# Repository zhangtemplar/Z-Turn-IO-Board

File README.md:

# Z-Turn-IO-Board
my own expansion board which converts the 1.27mm pitch connector to 2.54mm pitch connector for Z-turn board (http://www.myirtech.com/list.asp?id=502) from MYiR

###
A lot of design is borrowed from the IO Cape board (http://www.myirtech.com/list.asp?id=532) of MYiR, where I converts the Connector 1 to 6 PMOD compatible (2.54 mm dual row 12 pin header) headers and 1 40 pin FFC/FPC connector (for LCD); and Connector 2 to 2 PMOD headers plus 2 2.54mm dual row 34 pin header. Especially:

Connector | Comments
--------- | --------
CN1, CN2 | two 1.27mm pitch dual row 80 pin headers from Z-turn board
J1,J2|two 2.54mm pitch dual row 34 pin headers for FPGA differential pin (12 pairs each);
LCD|40 pin FFC/FPC connector;
MISC|PMOD header for I2C;
I2S|PMOD header for I2S and HDMI;
J3, J4, J5, J6|PMOD header for FPGA differential pin (4 pairs each);
ADC|PMOD header for XADC input (two pairs of analog input);
MIO|PMOD header for ARM IO pin (8 pins);
Note|the differential pins is not ready for high speed differential usage yet, as the length is not properly configured.

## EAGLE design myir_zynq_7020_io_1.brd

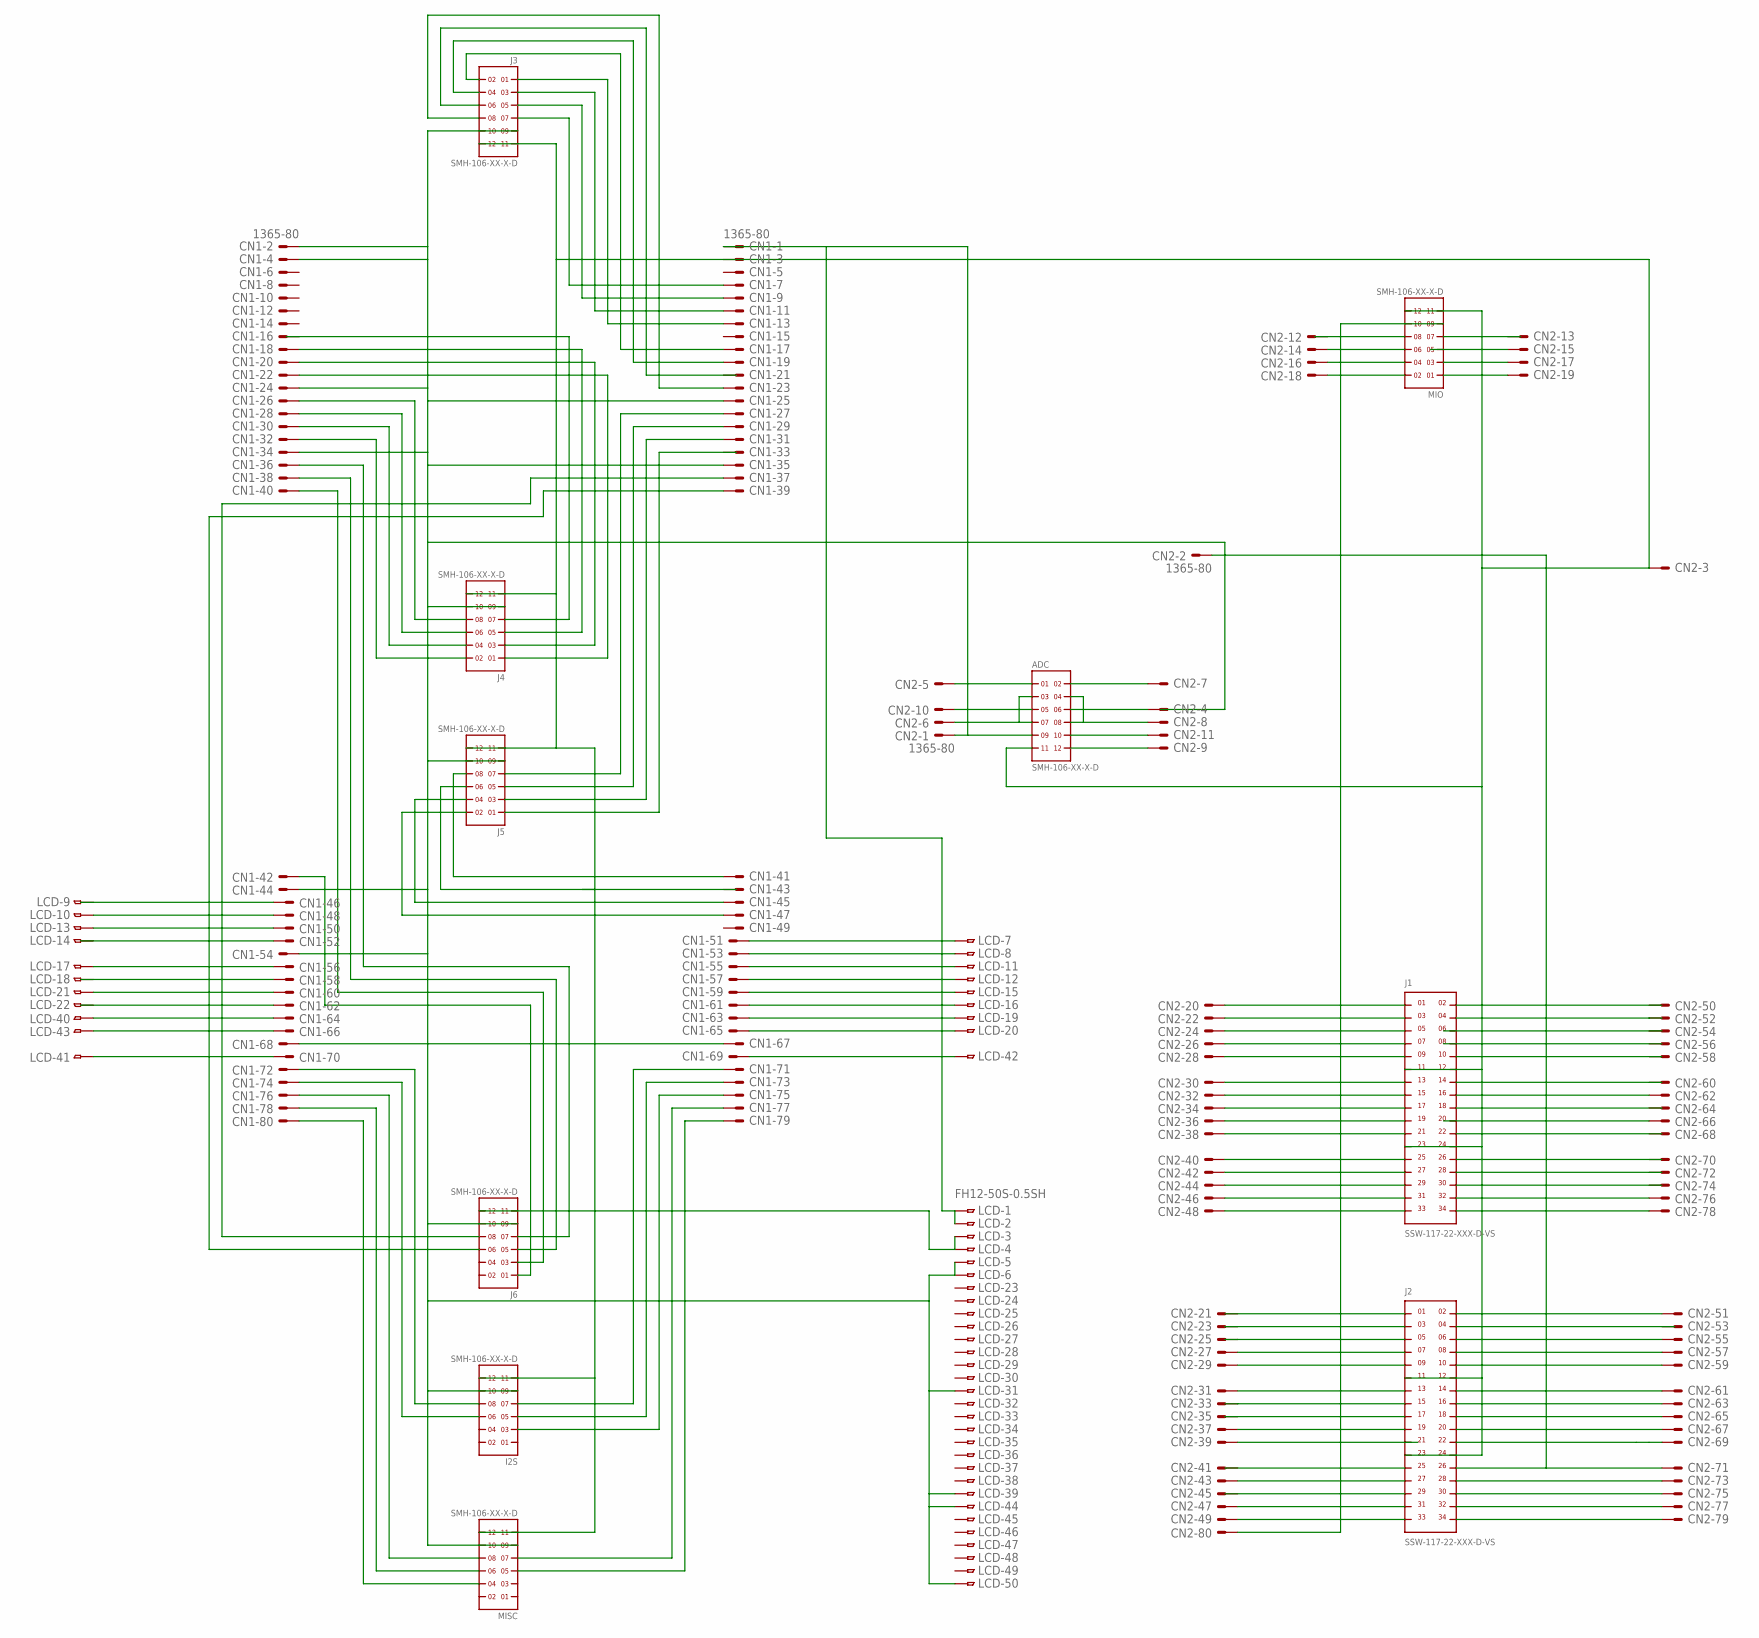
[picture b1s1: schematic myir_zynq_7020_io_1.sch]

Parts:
ADC: SMH-106-XX-X-D
CN1, CN2: 1365-80
I2S: SMH-106-XX-X-D
J1, J2: SSW-117-22-XXX-D-VS
J3, J4, J5, J6: SMH-106-XX-X-D
LCD: FH12-50S-0.5SH
MIO: SMH-106-XX-X-D
MISC: SMH-106-XX-X-D

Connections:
unnamed: CN1.70, LCD.41
unnamed: CN1.53, LCD.8
unnamed: CN1.66, LCD.43
unnamed: CN1.7, J3.7
unnamed: CN1.9, J3.5
unnamed: CN1.11, J3.3
unnamed: CN1.13, J3.1
unnamed: CN1.64, LCD.40
unnamed: CN1.40, J6.3
unnamed: CN1.38, J6.5
unnamed: CN1.36, J6.7
unnamed: CN1.42, J6.1
unnamed: CN1.27, J5.7
unnamed: CN1.29, J5.5
unnamed: CN1.31, J5.3
unnamed: ADC.11, CN1.3, CN2.3, I2S.11, I2S.12, J1.11, J1.12, J1.23, J1.24, J2.11, J2.12, J2.23, J2.24, J3.11, J3.12, J4.11, J4.12, J5.6, J5.11, J5.12, J6.11, J6.12, LCD.3, LCD.4, MIO.11, MIO.12, MISC.11, MISC.12
unnamed: CN1.41, J5.8
unnamed: CN1.37, J6.8
unnamed: CN1.39, J6.6
unnamed: CN1.45, J5.4
unnamed: CN1.51, LCD.7
unnamed: CN2.62, J1.16
unnamed: CN1.55, LCD.11
unnamed: CN1.71, I2S.7
unnamed: CN1.73, I2S.5
unnamed: CN1.75, I2S.3
unnamed: CN1.77, MISC.7
unnamed: CN1.79, MISC.5
unnamed: CN1.2, CN1.4, CN1.24, CN1.25, CN1.34, CN1.35, CN1.44, CN1.54, CN1.67, CN1.68, CN2.2, CN2.20, CN2.30, CN2.31, CN2.40, CN2.51, CN2.61, CN2.71, CN2.80, I2S.9, I2S.10, J1.1, J1.2, J1.13, J1.14, J1.25, J1.26, J2.1, J2.2, J2.13, J2.14, J2.25, J2.26, J3.9, J3.10, J4.9, J4.10, J5.9, J5.10, J6.9, J6.10, LCD.5, LCD.6, LCD.31, LCD.39, LCD.44, LCD.50, MIO.9, MIO.10, MISC.9, MISC.10
unnamed: CN1.57, LCD.12
unnamed: CN2.76, J1.32
unnamed: CN2.69, J2.22
unnamed: CN2.67, J2.20
unnamed: CN2.65, J2.18
unnamed: CN2.63, J2.16
unnamed: CN1.16, J4.7
unnamed: CN1.18, J4.5
unnamed: CN1.20, J4.3
unnamed: CN1.17, J3.2
unnamed: CN1.59, LCD.15
unnamed: CN1.26, J4.8
unnamed: CN1.28, J4.6
unnamed: CN1.30, J4.4
unnamed: CN1.61, LCD.16
unnamed: CN1.32, J4.2
unnamed: CN1.63, LCD.19
unnamed: CN1.65, LCD.20
unnamed: CN2.18, MIO.2
unnamed: CN2.59, J2.10
unnamed: CN2.57, J2.8
unnamed: CN2.55, J2.6
unnamed: CN2.16, MIO.4
unnamed: CN2.78, J1.34
unnamed: CN2.22, J1.3
unnamed: CN2.24, J1.5
unnamed: CN2.26, J1.7
unnamed: CN1.48, LCD.10
unnamed: CN2.28, J1.9
unnamed: CN1.72, I2S.8
unnamed: CN1.74, I2S.6
unnamed: CN1.76, MISC.8
unnamed: CN1.78, MISC.6
unnamed: CN1.80, MISC.4
unnamed: CN2.14, MIO.6
unnamed: CN2.17, MIO.3
unnamed: CN2.19, MIO.1
unnamed: CN2.27, J2.7
unnamed: ADC.12, CN2.9
unnamed: CN2.29, J2.9
unnamed: ADC.2, CN2.7
unnamed: CN2.32, J1.15
unnamed: CN2.34, J1.17
unnamed: CN2.36, J1.19
unnamed: CN2.38, J1.21
unnamed: ADC.1, CN2.5
unnamed: ADC.10, CN2.11
unnamed: CN2.25, J2.5
unnamed: CN2.37, J2.19
unnamed: ADC.4, ADC.8, CN2.8
unnamed: CN2.43, J2.27
unnamed: CN2.47, J2.31
unnamed: CN2.49, J2.33
unnamed: ADC.3, ADC.7, CN2.6
unnamed: CN2.33, J2.15
unnamed: ADC.5, CN2.10
unnamed: ADC.6, CN2.4
unnamed: CN1.47, J5.2
unnamed: CN1.22, J4.1
unnamed: CN1.19, J3.4
unnamed: CN2.73, J2.28
unnamed: CN2.75, J2.30
unnamed: CN2.77, J2.32
unnamed: CN2.79, J2.34
unnamed: CN1.23, J3.8
unnamed: CN2.52, J1.4
unnamed: CN1.50, LCD.13
unnamed: CN1.56, LCD.17
unnamed: CN1.60, LCD.21
unnamed: ADC.9, CN1.1, CN2.1, LCD.1, LCD.2
unnamed: CN1.69, LCD.42

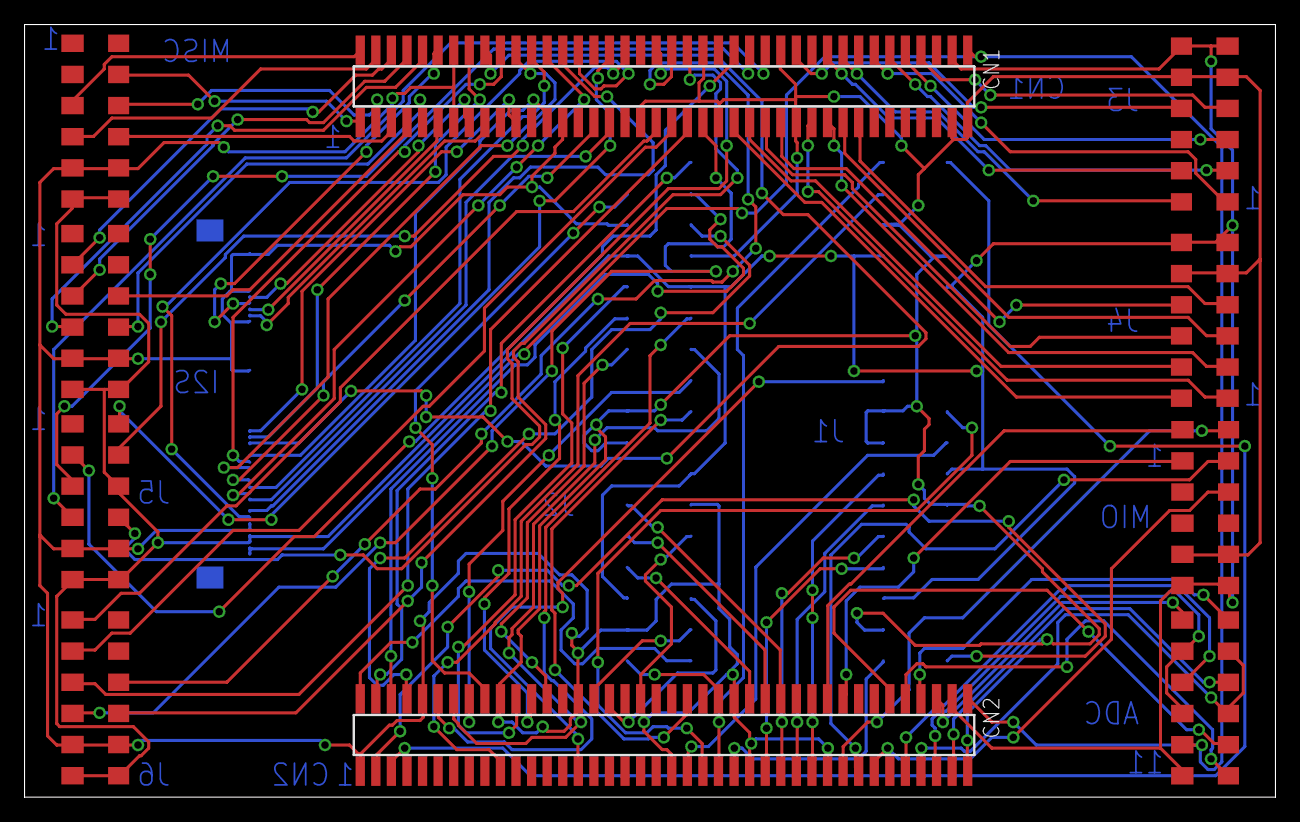
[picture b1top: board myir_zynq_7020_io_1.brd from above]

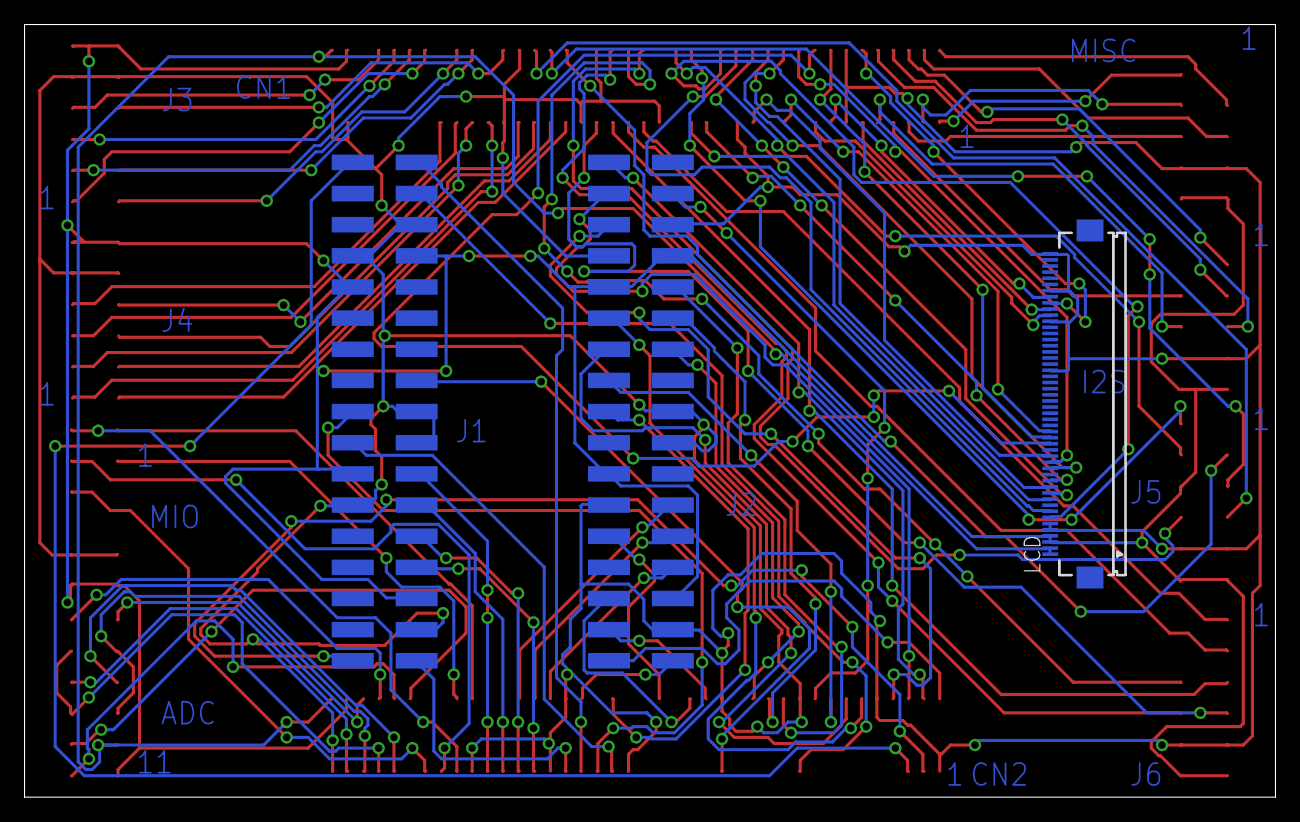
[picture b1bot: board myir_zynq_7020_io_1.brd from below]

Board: 2 copper layers, 102.0 x 63.0 mm, 13 parts (3 on the bottom side), 100 nets.
